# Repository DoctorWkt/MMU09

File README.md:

# MMU09 - A 6809 single-board computer with an MMU

I'm working on a 6809 single-board computer with an external MMU, so I can
bring up a Unix-like operating system for it. Currently this is the `xv6`
filesystem with process code partially borrowed from `xv6`. The library 
comes from FUZIX and the userland comes from multiple places, some
self-written.

The [Hardware](Hardware) folder has the hardware version of the system.
The main components are: the 6809, 32K ROM, 512K RAM, a dual UART, a
CH375 device for storage and an ATF1508 CPLD to implement address decoding
and the MMU.

The [Docs](Docs) folder has details of the design and the implementation.

The [Verilog](Verilog) folder has the Verilog code for the CPLD as well as
a Verilog implementation of the 6809, ROM, RAM and a UART. This allows me to
test the MMU to ensure that it will work before I build the hardware.

I'd really like to get some feedback, ideas etc. on this project.

## Status - 1st September 2023

I've updated the schematic with the pin headers to make the PCB into a "hat"
which will sit on top of an Atmega 2560. I'll be able to use this to monitor
and partially control the SBC.

I've made a first attempt at laying out the components on a PCB, and there
is an archive of the Kicad project in the [Hardware](Hardware) folder.

In the [Verilog](Verilog) folder, there is now an Icarus Verilog simulation of the
system. I can run 6809 instructions and see the system go in/out of kernel
mode, and see the page mappings change.

The CPLD Verilog code now has reset functionality.

## Status - 10th September 2023

I now have a completed PCB design; see the [Hardware](Hardware) folder for a schematic
and views of the PC board.

## Status - 18th September 2023

I have ported the xv6 filesystem code from [https://github.com/DoctorWkt/Nine-E/](https://github.com/DoctorWkt/Nine-E/).
This gives me a Unix-like environment but with only one program running at a time.
I've used the address decoding on the MMU09 to give each program 63.5K of address
space. This works in the Salmi simulator.

I've ordered the PCB and the parts to build the hardware; they haven't arrived yet, sigh.

## Status - 4th October 2023

I've built the board and, with the exception of the DS12C887, everything
works at 14.75MHz. I've changed the CPLD code to have a stack of four
previous user/kernel modes; this allows us to go from user mode to kernel
mode, followed by two nested interrupts, and return safely back to user mode.

Programming the CPLD with the Verilog -> Yosys -> JED workflow is nice and
easy, using the workflow from [https://github.com/hoglet67/atf15xx_yosys](https://github.com/hoglet67/atf15xx_yosys).
I'm then using the `jed2svf` converter from
[https://whitequark.github.io/prjbureau/tools/fuseconv.html](https://whitequark.github.io/prjbureau/tools/fuseconv.html) to make the
SVF file, and a FT232H device and OpenOCD to send the SVF file to the ATF1508 CPLD,
based on the information from
[https://www.hackup.net/2020/01/erasing-and-programming-the-atf1504-cpld/](https://www.hackup.net/2020/01/erasing-and-programming-the-atf1504-cpld/).

I have a simple monitor which allows me to dump memory contents,
alter memory and run a program in user mode. There are syscalls to read from
& write to the UART, and to exit back to the monitor.

## Status - 17th October 2023

After fighting a problem with RAM for over a week, I found that my Verilog code
for the RAM chip select was wrong. Now fixed. This allows me to get the xv6
filesystem code up and running on the board. Each program now has a usable address
space of $0000 to $FDFF, with the constraint that only code can be in $0000 to $1FFF.

## Status - December 2023

Things have been rearranged. I now have processes and multitasking, but
no pre-emption as yet. There is `fork()`, `exec()`, `exit()` and `wait()`
along with `pipe()`.

I got the wiring of the RTC wrong, but I should be able to use the CPLD
to generate clock ticks and do time keeping and pre-emption this way.

I need to rewrite the shell to do file redirection in the child, not in the
parent process. The shell worked when there was only one process; this is
no longer the case.

Processes now have 63.5K of address space with the constraint that the lower
8K of address space cannot contain any data.

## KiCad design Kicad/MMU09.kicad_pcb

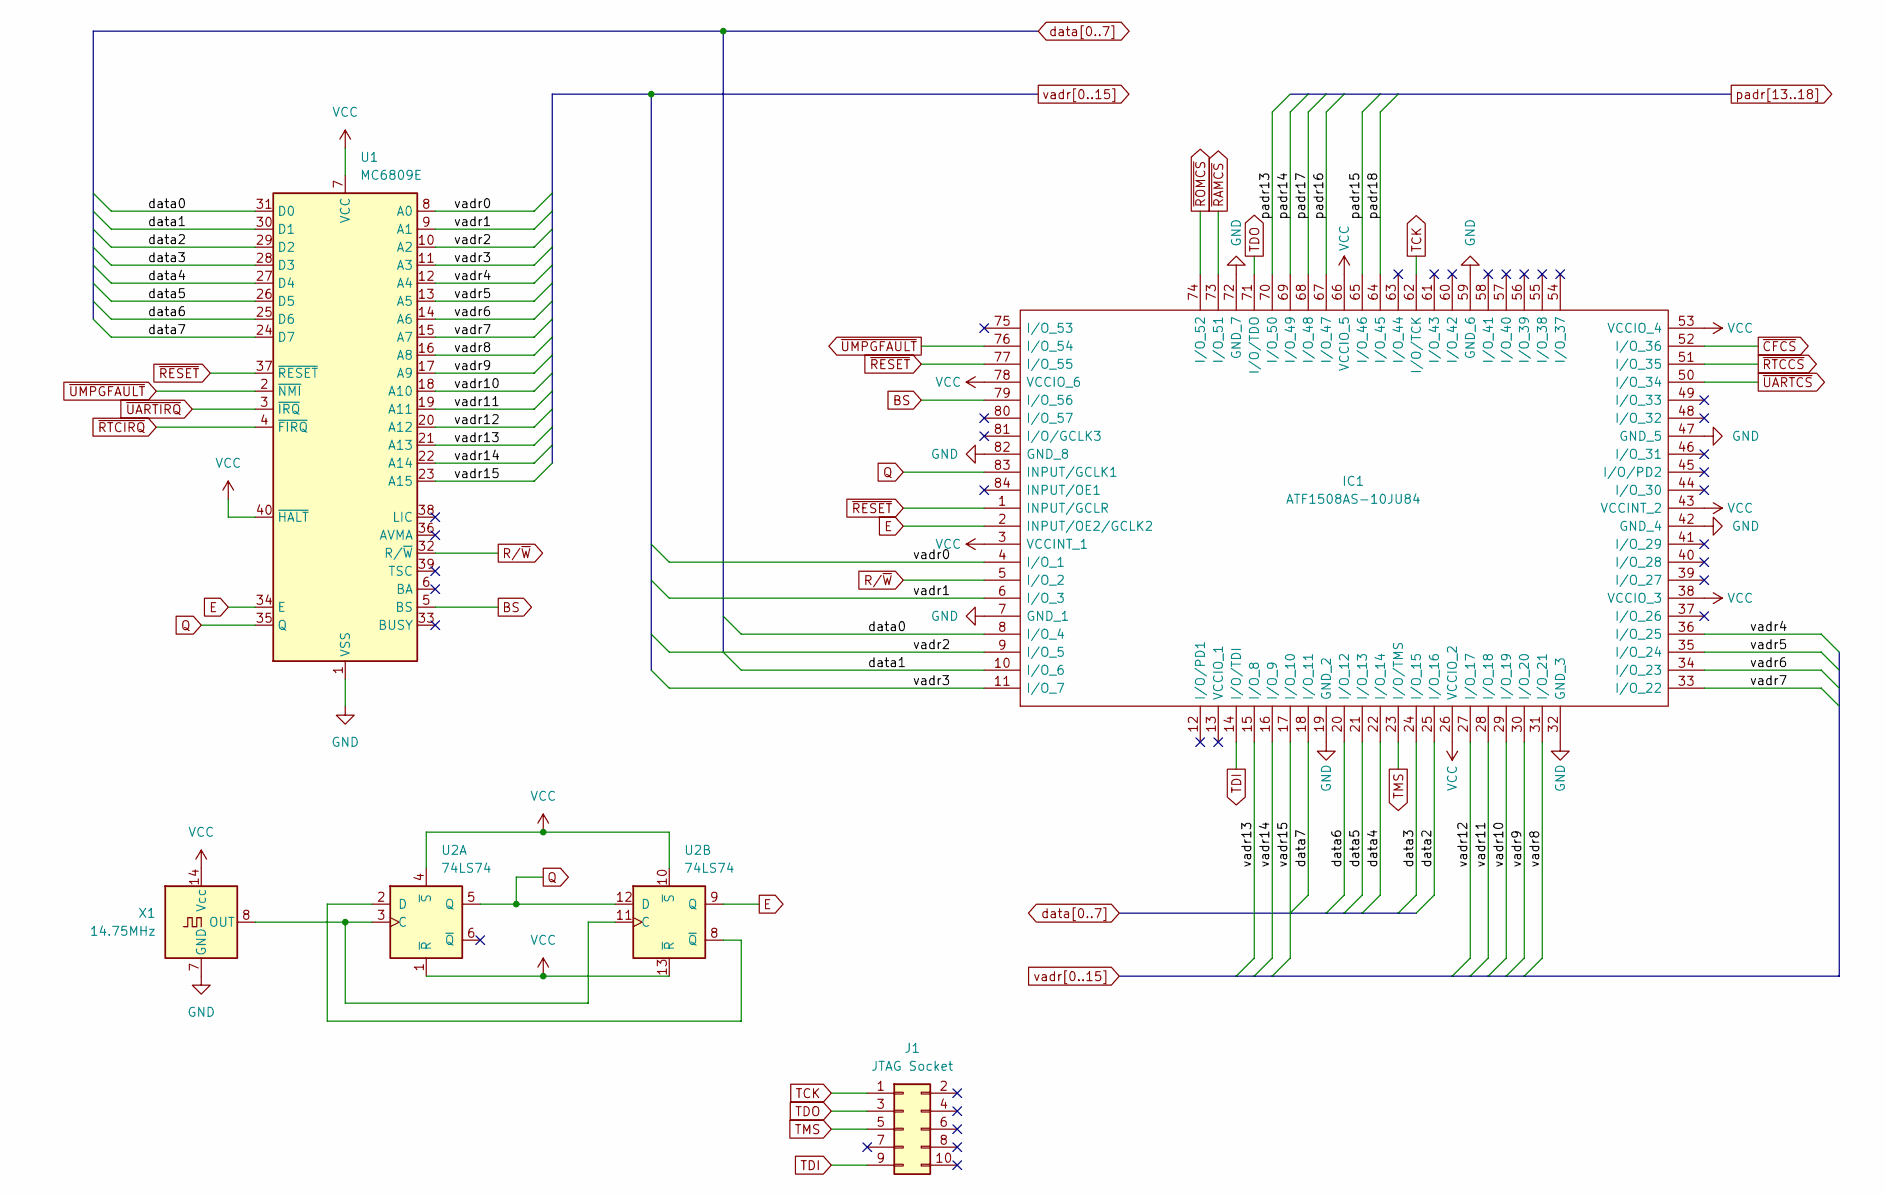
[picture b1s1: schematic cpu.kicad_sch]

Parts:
IC1: ATF1508AS-10JU84; PLCC127P3010X3010X457-84N; Manufacturer_Part_Number ATF1508AS-10JU84; Mouser Part Number 556-ATF1508AS-10JU84
J1: JTAG Socket; PinHeader_2x05_P2.54mm_Vertical
U1: MC6809E; DIP-40_W15.24mm
U2: 74LS74; DIP-14_W7.62mm
X1: 14.75MHz; Oscillator_DIP-14

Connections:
BS: IC1.79 (I/O_56), U1.5 (BS)
E: IC1.2 (INPUT/OE2/GCLK2), U1.34 (E), U2.9 (Q); also elsewhere on the board
GND: IC1.7 (GND_1), IC1.19 (GND_2), IC1.32 (GND_3), IC1.42 (GND_4), IC1.47 (GND_5), IC1.59 (GND_6), IC1.72 (GND_7), IC1.82 (GND_8), U1.1 (VSS), X1.7 (GND); also elsewhere on the board
unnamed: U2.2 (D), U2.8 (~Q)
unnamed: U2.3 (C), U2.11 (C), X1.8 (OUT)
Q: IC1.83 (INPUT/GCLK1), U1.35 (Q), U2.5 (Q), U2.12 (D)
R/~W: IC1.5 (I/O_2), U1.32 (R/~W); also elsewhere on the board
TCK: IC1.62 (I/O/TCK), J1.1
TDI: IC1.14 (I/O/TDI), J1.9
TDO: IC1.71 (I/O/TDO), J1.3
TMS: IC1.23 (I/O/TMS), J1.5
VCC: IC1.3 (VCCINT_1), IC1.26 (VCCIO_2), IC1.38 (VCCIO_3), IC1.43 (VCCINT_2), IC1.53 (VCCIO_4), IC1.66 (VCCIO_5), IC1.78 (VCCIO_6), U1.7 (VCC), U1.40 (~HALT), U2.1 (~R), U2.4 (~S), U2.10 (~S), U2.13 (~R), X1.14 (Vcc); also elsewhere on the board
data0: IC1.8 (I/O_4), U1.31 (D0); also elsewhere on the board
data1: IC1.10 (I/O_6), U1.30 (D1); also elsewhere on the board
data2: IC1.25 (I/O_16), U1.29 (D2); also elsewhere on the board
data3: IC1.24 (I/O_15), U1.28 (D3); also elsewhere on the board
data4: IC1.22 (I/O_14), U1.27 (D4); also elsewhere on the board
data5: IC1.21 (I/O_13), U1.26 (D5); also elsewhere on the board
data6: IC1.20 (I/O_12), U1.25 (D6); also elsewhere on the board
data7: IC1.18 (I/O_11), U1.24 (D7); also elsewhere on the board
padr13: IC1.70 (I/O_50); also elsewhere on the board
padr14: IC1.69 (I/O_49); also elsewhere on the board
padr15: IC1.65 (I/O_46); also elsewhere on the board
padr16: IC1.67 (I/O_47); also elsewhere on the board
padr17: IC1.68 (I/O_48); also elsewhere on the board
padr18: IC1.64 (I/O_45); also elsewhere on the board
vadr0: IC1.4 (I/O_1), U1.8 (A0); also elsewhere on the board
vadr1: IC1.6 (I/O_3), U1.9 (A1); also elsewhere on the board
vadr2: IC1.9 (I/O_5), U1.10 (A2); also elsewhere on the board
vadr3: IC1.11 (I/O_7), U1.11 (A3); also elsewhere on the board
vadr4: IC1.36 (I/O_25), U1.12 (A4); also elsewhere on the board
vadr5: IC1.35 (I/O_24), U1.13 (A5); also elsewhere on the board
vadr6: IC1.34 (I/O_23), U1.14 (A6); also elsewhere on the board
vadr7: IC1.33 (I/O_22), U1.15 (A7); also elsewhere on the board
vadr8: IC1.31 (I/O_21), U1.16 (A8); also elsewhere on the board
vadr9: IC1.30 (I/O_20), U1.17 (A9); also elsewhere on the board
vadr10: IC1.29 (I/O_19), U1.18 (A10); also elsewhere on the board
vadr11: IC1.28 (I/O_18), U1.19 (A11); also elsewhere on the board
vadr12: IC1.27 (I/O_17), U1.20 (A12); also elsewhere on the board
vadr13: IC1.15 (I/O_8), U1.21 (A13); also elsewhere on the board
vadr14: IC1.16 (I/O_9), U1.22 (A14); also elsewhere on the board
vadr15: IC1.17 (I/O_10), U1.23 (A15)
~CFCS: IC1.52 (I/O_36); also elsewhere on the board
~RAMCS: IC1.73 (I/O_51); also elsewhere on the board
~RESET: IC1.1 (INPUT/GCLR), IC1.77 (I/O_55), U1.37 (~RESET); also elsewhere on the board
~ROMCS: IC1.74 (I/O_52); also elsewhere on the board
~RTCCS: IC1.51 (I/O_35); also elsewhere on the board
~RTCIRQ: U1.4 (~FIRQ); also elsewhere on the board
~UARTCS: IC1.50 (I/O_34); also elsewhere on the board
~UARTIRQ: U1.3 (~IRQ); also elsewhere on the board
~UMPGFAULT: IC1.76 (I/O_54), U1.2 (~NMI)

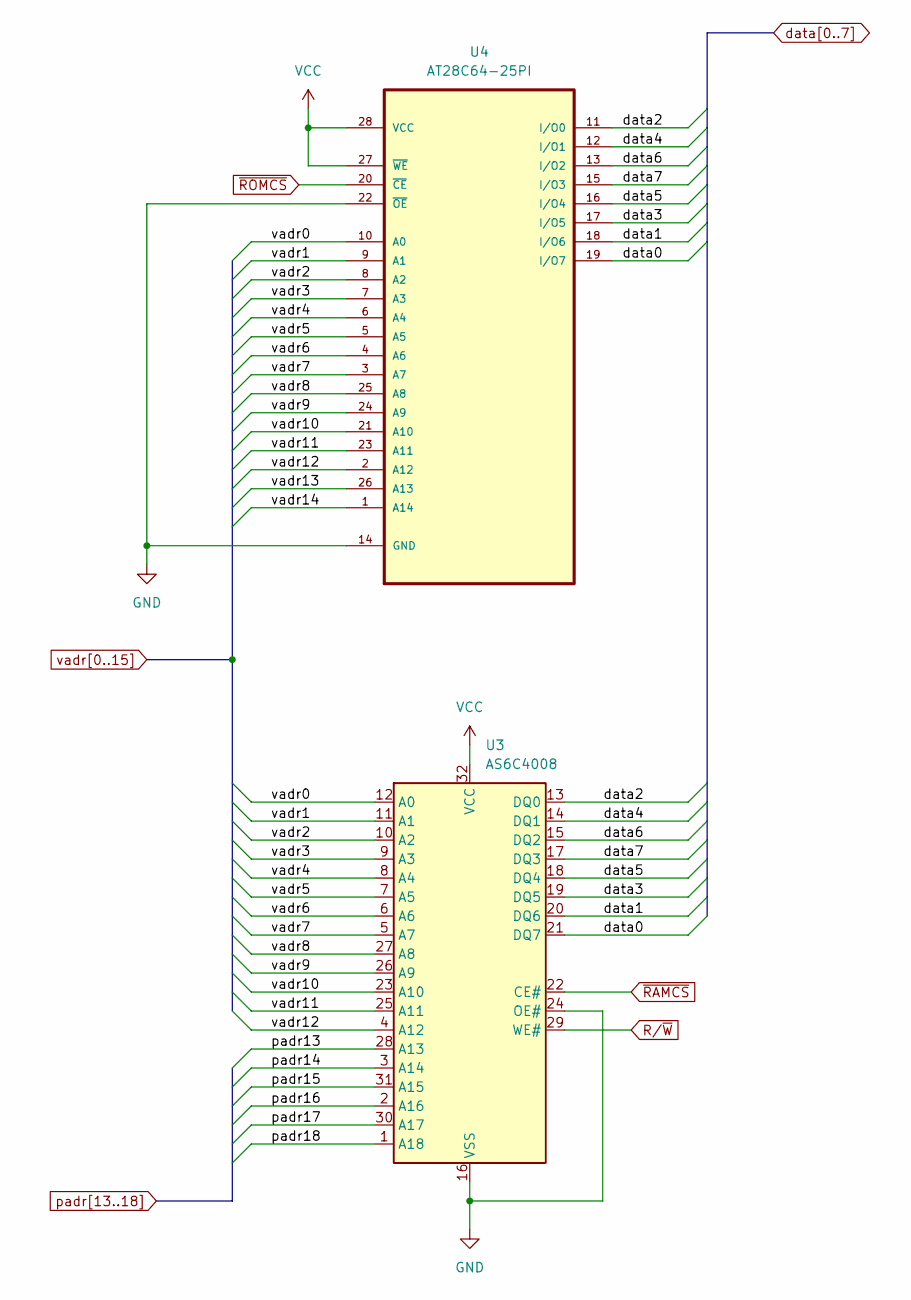
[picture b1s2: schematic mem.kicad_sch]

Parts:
U3: AS6C4008; DIP-32_W15.24mm
U4: AT28C64-25PI; DIP-28_W15.24mm; MPN AT28C64-25PI

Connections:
GND: U3.16 (VSS), U3.24 (OE#), U4.14 (GND), U4.22 (~OE); also elsewhere on the board
R/~W: U3.29 (WE#); also elsewhere on the board
VCC: U3.32 (VCC), U4.27 (~WE), U4.28 (VCC); also elsewhere on the board
data0: U3.21 (DQ7), U4.19 (I/O7); also elsewhere on the board
data1: U3.20 (DQ6), U4.18 (I/O6); also elsewhere on the board
data2: U3.13 (DQ0), U4.11 (I/O0); also elsewhere on the board
data3: U3.19 (DQ5), U4.17 (I/O5); also elsewhere on the board
data4: U3.14 (DQ1), U4.12 (I/O1); also elsewhere on the board
data5: U3.18 (DQ4), U4.16 (I/O4); also elsewhere on the board
data6: U3.15 (DQ2), U4.13 (I/O2); also elsewhere on the board
data7: U3.17 (DQ3), U4.15 (I/O3); also elsewhere on the board
padr13: U3.28 (A13); also elsewhere on the board
padr14: U3.3 (A14); also elsewhere on the board
padr15: U3.31 (A15); also elsewhere on the board
padr16: U3.2 (A16); also elsewhere on the board
padr17: U3.30 (A17); also elsewhere on the board
padr18: U3.1 (A18); also elsewhere on the board
vadr0: U3.12 (A0), U4.10 (A0); also elsewhere on the board
vadr1: U3.11 (A1), U4.9 (A1); also elsewhere on the board
vadr2: U3.10 (A2), U4.8 (A2); also elsewhere on the board
vadr3: U3.9 (A3), U4.7 (A3); also elsewhere on the board
vadr4: U3.8 (A4), U4.6 (A4); also elsewhere on the board
vadr5: U3.7 (A5), U4.5 (A5); also elsewhere on the board
vadr6: U3.6 (A6), U4.4 (A6); also elsewhere on the board
vadr7: U3.5 (A7), U4.3 (A7); also elsewhere on the board
vadr8: U3.27 (A8), U4.25 (A8); also elsewhere on the board
vadr9: U3.26 (A9), U4.24 (A9); also elsewhere on the board
vadr10: U3.23 (A10), U4.21 (A10); also elsewhere on the board
vadr11: U3.25 (A11), U4.23 (A11); also elsewhere on the board
vadr12: U3.4 (A12), U4.2 (A12); also elsewhere on the board
vadr13: U4.26 (A13); also elsewhere on the board
vadr14: U4.1 (A14); also elsewhere on the board
~RAMCS: U3.22 (CE#); also elsewhere on the board
~ROMCS: U4.20 (~CE); also elsewhere on the board

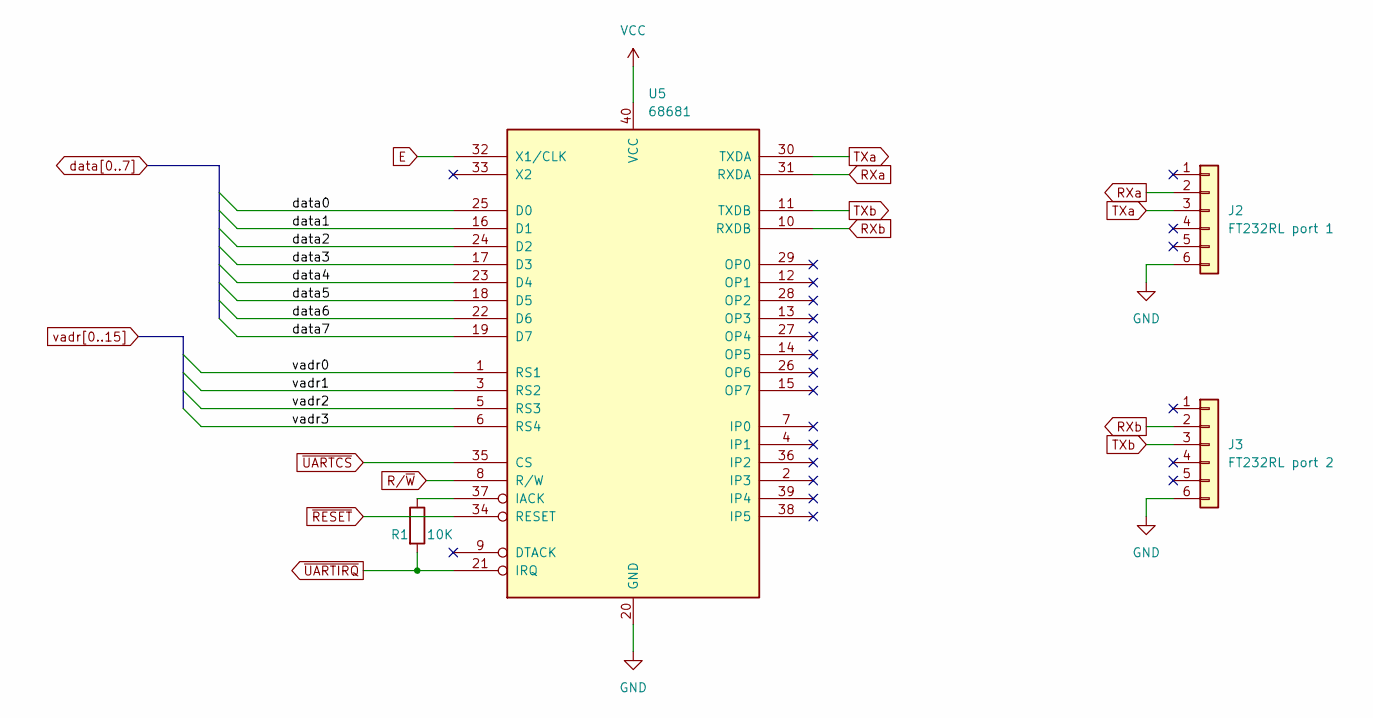
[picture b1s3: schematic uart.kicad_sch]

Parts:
J2: FT232RL port 1; PinHeader_1x06_P2.54mm_Vertical
J3: FT232RL port 2; PinHeader_1x06_P2.54mm_Vertical
R1: 10K; R_0603_1608Metric_Pad0.98x0.95mm_HandSolder
U5: 68681; DIP-40_W15.24mm

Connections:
E: U5.32 (X1/CLK); also elsewhere on the board
GND: J2.6, J3.6, U5.20 (GND); also elsewhere on the board
unnamed: R1.1, U5.37 (IACK)
RXa: J2.2, U5.31 (RXDA)
RXb: J3.2, U5.10 (RXDB)
R/~W: U5.8 (R/W); also elsewhere on the board
TXa: J2.3, U5.30 (TXDA)
TXb: J3.3, U5.11 (TXDB)
VCC: U5.40 (VCC); also elsewhere on the board
data0: U5.25 (D0); also elsewhere on the board
data1: U5.16 (D1); also elsewhere on the board
data2: U5.24 (D2); also elsewhere on the board
data3: U5.17 (D3); also elsewhere on the board
data4: U5.23 (D4); also elsewhere on the board
data5: U5.18 (D5); also elsewhere on the board
data6: U5.22 (D6); also elsewhere on the board
data7: U5.19 (D7); also elsewhere on the board
vadr0: U5.1 (RS1); also elsewhere on the board
vadr1: U5.3 (RS2); also elsewhere on the board
vadr2: U5.5 (RS3); also elsewhere on the board
vadr3: U5.6 (RS4); also elsewhere on the board
~RESET: U5.34 (RESET); also elsewhere on the board
~UARTCS: U5.35 (CS); also elsewhere on the board
~UARTIRQ: R1.2, U5.21 (IRQ); also elsewhere on the board

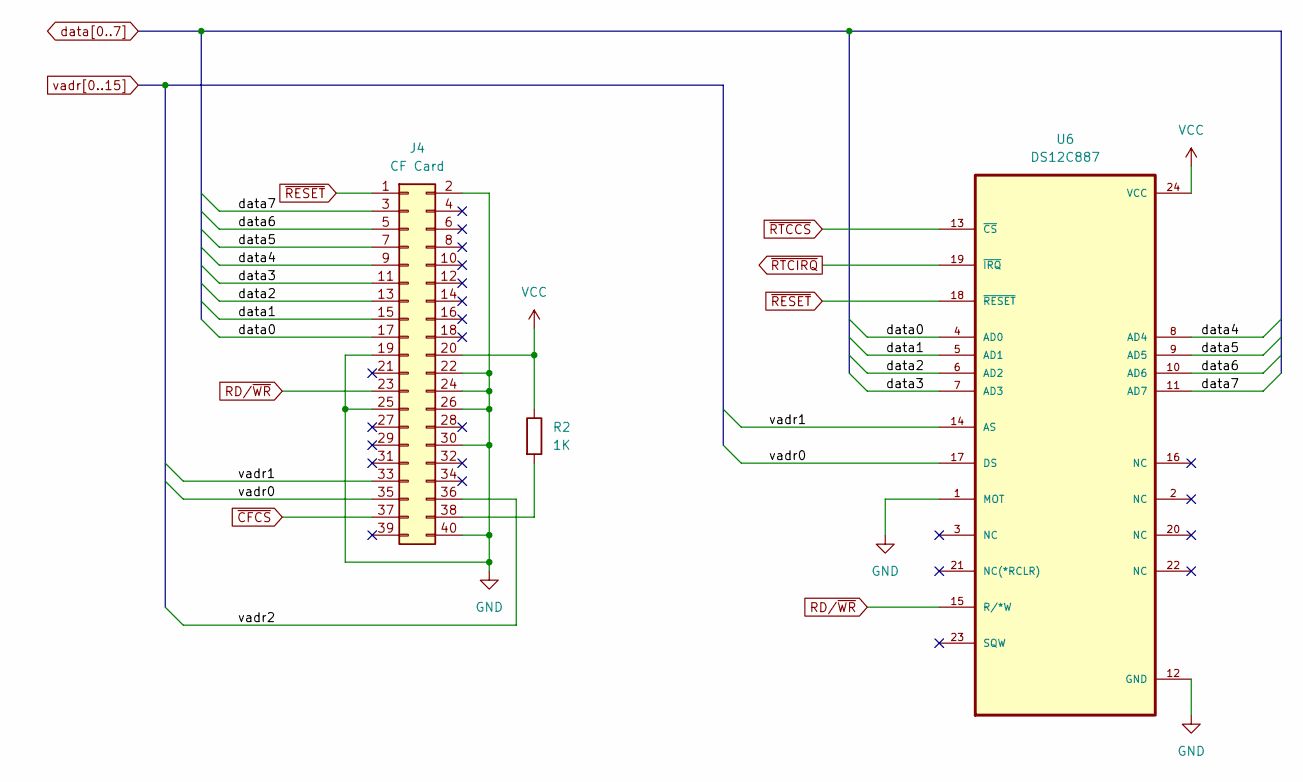
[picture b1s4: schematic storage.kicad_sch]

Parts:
J4: CF Card; PinHeader_2x20_P2.54mm_Vertical
R2: 1K; R_0603_1608Metric_Pad0.98x0.95mm_HandSolder
U6: DS12C887; DIP-24_W10.16mm

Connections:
GND: J4.2, J4.19, J4.22, J4.24, J4.25, J4.26, J4.30, J4.40, U6.1 (MOT), U6.12 (GND); also elsewhere on the board
unnamed: J4.38, R2.2
RD/~WR: J4.23, U6.15 (R/*W)
VCC: J4.20, R2.1, U6.24 (VCC); also elsewhere on the board
data0: J4.17, U6.4 (AD0); also elsewhere on the board
data1: J4.15, U6.5 (AD1); also elsewhere on the board
data2: J4.13, U6.6 (AD2); also elsewhere on the board
data3: J4.11, U6.7 (AD3); also elsewhere on the board
data4: J4.9, U6.8 (AD4); also elsewhere on the board
data5: J4.7, U6.9 (AD5); also elsewhere on the board
data6: J4.5, U6.10 (AD6); also elsewhere on the board
data7: J4.3, U6.11 (AD7); also elsewhere on the board
vadr0: J4.35, U6.17 (DS); also elsewhere on the board
vadr1: J4.33, U6.14 (AS); also elsewhere on the board
vadr2: J4.36; also elsewhere on the board
~CFCS: J4.37; also elsewhere on the board
~RESET: J4.1, U6.18 (~RESET); also elsewhere on the board
~RTCCS: U6.13 (~CS); also elsewhere on the board
~RTCIRQ: U6.19 (~IRQ); also elsewhere on the board

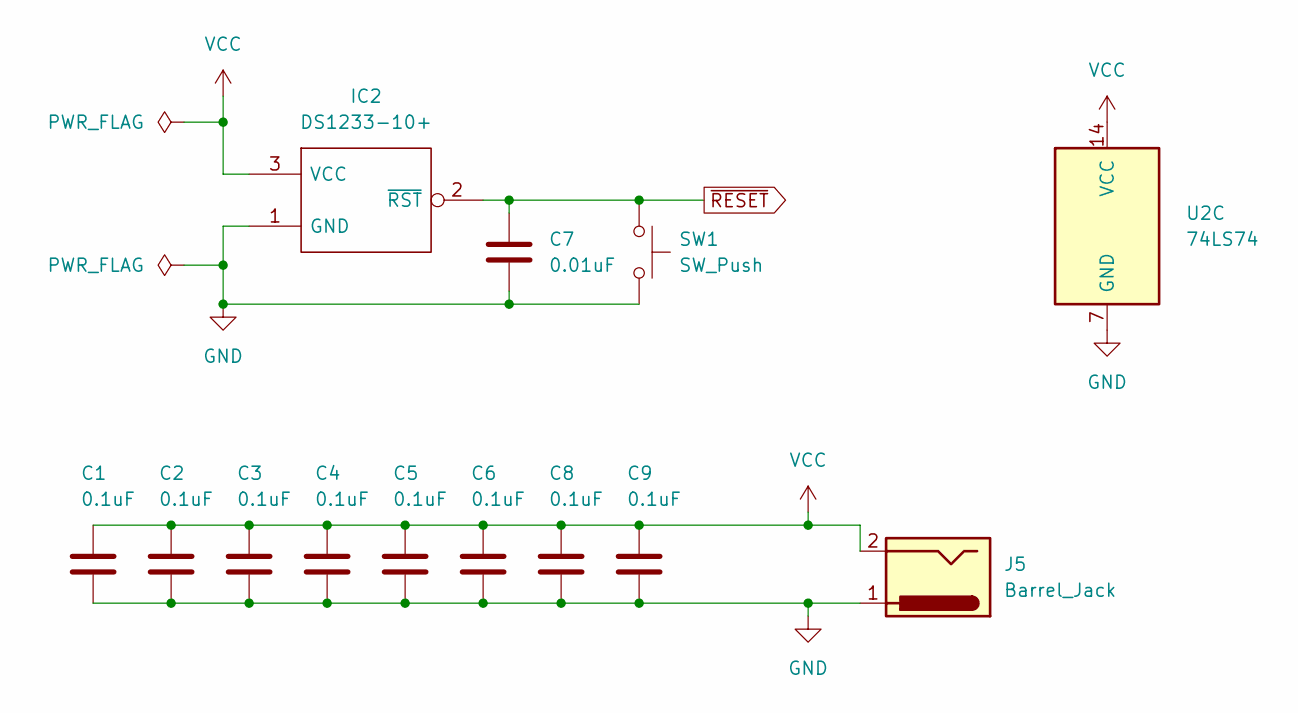
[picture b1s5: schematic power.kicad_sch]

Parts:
C1, C2, C3, C4, C5, C6, C8, C9: 0.1uF; C_0603_1608Metric_Pad1.08x0.95mm_HandSolder
C7: 0.01uF; C_0603_1608Metric_Pad1.08x0.95mm_HandSolder
IC2: DS1233-10+; TO-92; Manufacturer_Part_Number DS1233-10+; Mouser Part Number 700-DS1233-10
J5: Barrel_Jack; BarrelJack_SwitchcraftConxall_RAPC10U_Horizontal
SW1: SW_Push; Push_E-Switch_KS01Q01
U2: 74LS74; DIP-14_W7.62mm

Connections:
GND: C1.2, C2.2, C3.2, C4.2, C5.2, C6.2, C7.2, C8.2, C9.2, IC2.1 (GND), J5.1, SW1.2, U2.7 (GND); also elsewhere on the board
VCC: C1.1, C2.1, C3.1, C4.1, C5.1, C6.1, C8.1, C9.1, IC2.3 (VCC), J5.2, U2.14 (VCC); also elsewhere on the board
~RESET: C7.1, IC2.2 (~RST), SW1.1; also elsewhere on the board

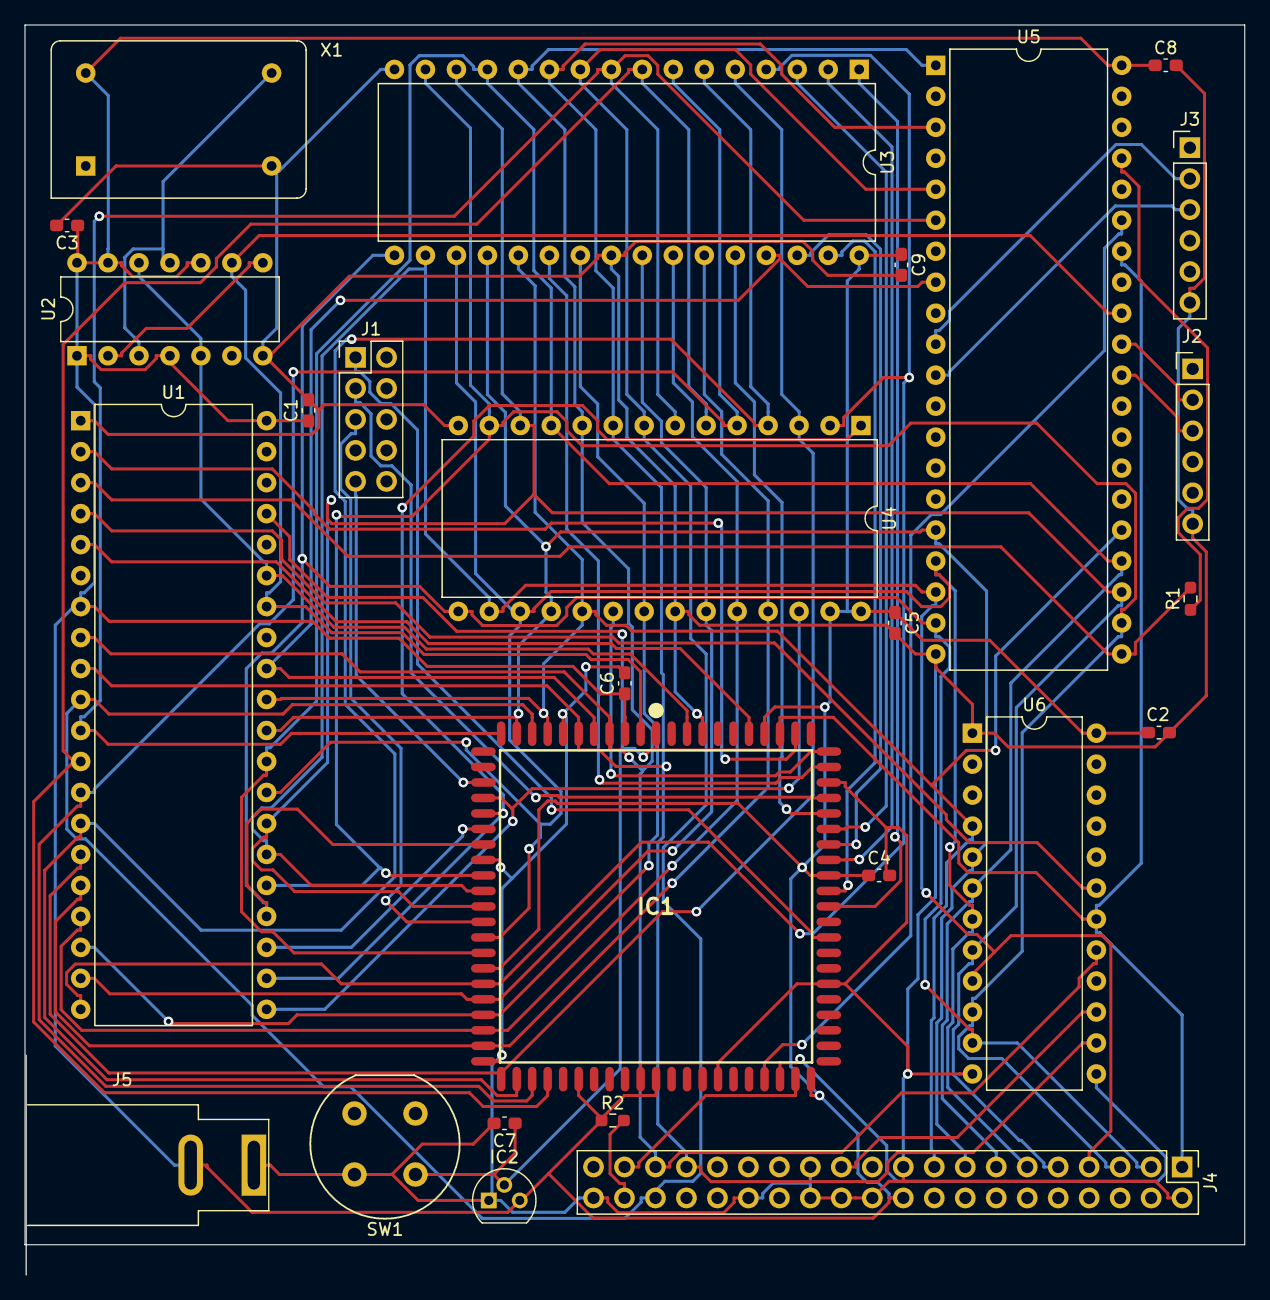
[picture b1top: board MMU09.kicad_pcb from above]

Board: 2 copper layers, 100.0 x 102.5 mm, 26 parts (0 on the bottom side), 58 nets.

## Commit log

2022-08-10 First upload of the files I've been working on.
2022-08-10 Added a design document.
2022-08-11 I'm now moving away from my compiler to the `cmoc` compiler. I've also imported the user-mode 6809 simulator that I'm extending.
2022-08-11 I split the OS interface code from the 6809 simulator.
2022-08-12 Added open(), close(), read() and write() to um6809
2022-08-15 More syscalls implemented in um6809.
2022-08-15 Updated the Kicad schematic PDF file.
2023-08-27 An initial set of documents to describe my proposed design and ask for feedback.
2023-08-31 Updated the schematic with pins for the Atmega 2560. Added reset functionality to the CPLD Verilog code. Imported the Icarus Verilog simulation code. Did an initial PCB layout.
2023-08-31 Added an image of the address map.
2023-09-10 Redesigned the schematic and PCB to be a better "hat" for the Mega 2560. Generated the gerbers for the PCB. Imported the Salmi simulator and added page table handling. Tidied up the Verilog code to g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
2023-09-10 Tidied up the memory code in the Salmi simulator and added my initial monitor code.
2023-09-18 I changed the memory layout back to have I/O at $FExx and ROM at $FFxx. I updated the documentation to reflect this, along with the Monitor code. I also updated the Salmi simulator to implement these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
2023-09-18 Updated top-level README.md.
2023-09-18 Bring the Verilog code for the MMU up to date.
2023-10-03 Added the stacking of user/kernel modes in the CPLD. Tested the CPLD code on the real hardware.
2023-10-03 Added the prevmode toggle to the monitor code.
2023-10-17 I got the XV6FS code to run on the SBC after fixing the Verilog code for the RAM chip select.
2023-12-08 We are now at the point where the system has non-pre-emptive multitasking and pipes. A process can block and a new process chosen to become the running process.
2023-12-08 Updated the design documentation.
